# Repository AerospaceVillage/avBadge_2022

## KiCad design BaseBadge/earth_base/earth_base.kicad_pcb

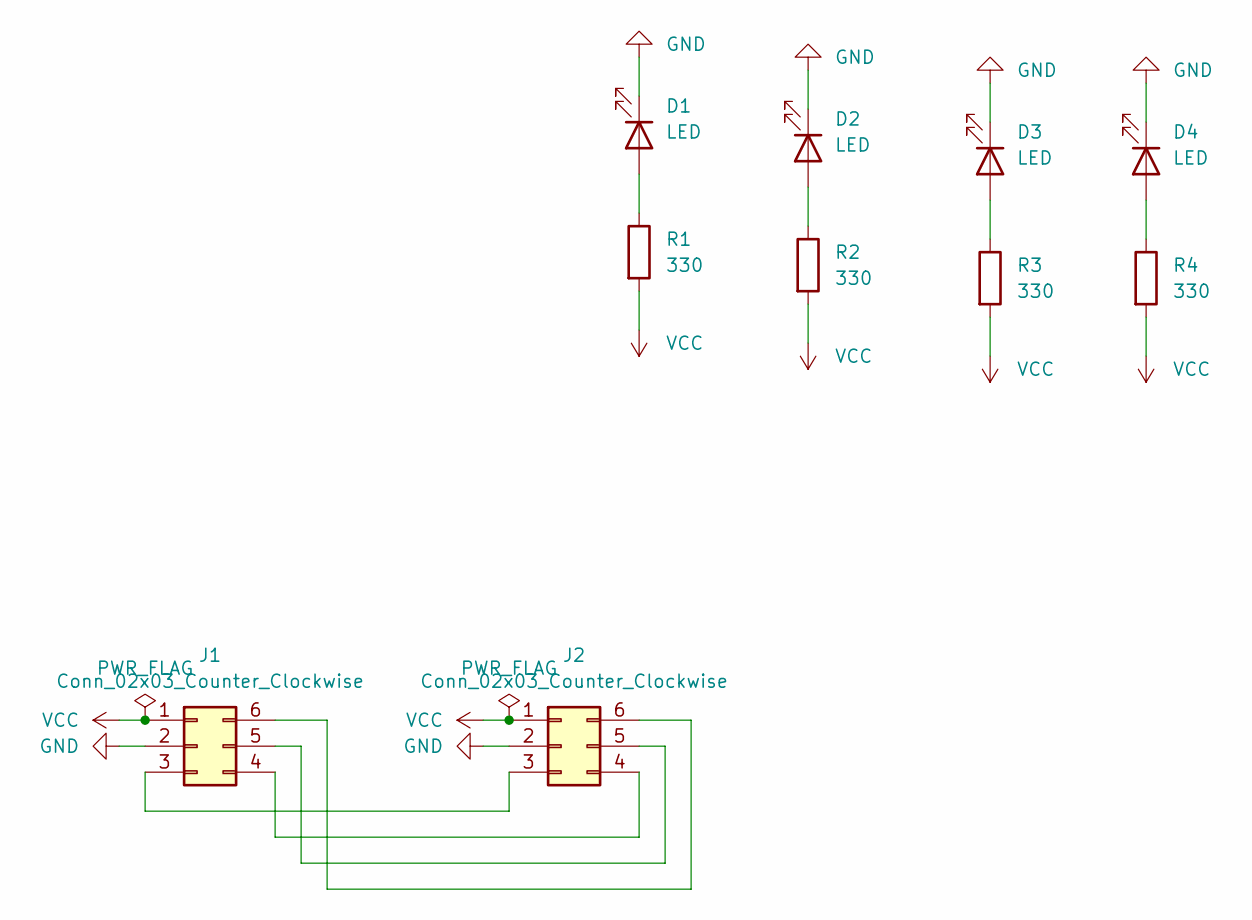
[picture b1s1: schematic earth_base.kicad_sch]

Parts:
D1, D2, D3, D4: LED
J1: Conn_02x03_Counter_Clockwise; sky2ground_connector
J2: Conn_02x03_Counter_Clockwise; PinSocket_2x03_P2.54mm_Vertical
R1, R2, R3, R4: 330; R_0805_2012Metric

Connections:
GND: D1.1 (K), D2.1 (K), D3.1 (K), D4.1 (K), J1.2, J2.2
unnamed: D1.2 (A), R1.1
unnamed: D2.2 (A), R2.1
unnamed: D3.2 (A), R3.1
unnamed: D4.2 (A), R4.1
unnamed: J1.3, J2.3
unnamed: J1.4, J2.4
unnamed: J1.5, J2.5
unnamed: J1.6, J2.6
VCC: J1.1, J2.1, R1.2, R2.2, R3.2, R4.2

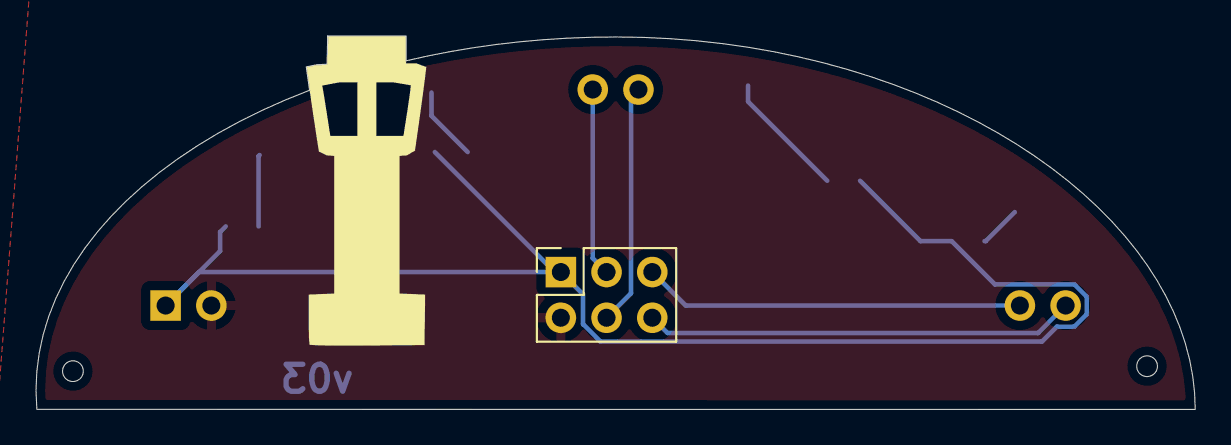
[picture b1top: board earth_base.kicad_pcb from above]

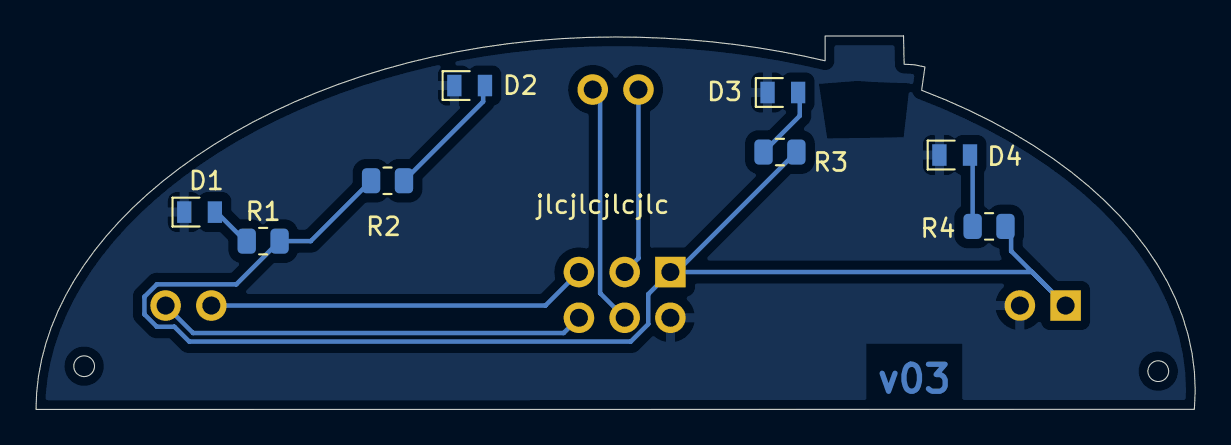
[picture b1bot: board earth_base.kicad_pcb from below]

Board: 2 copper layers, 64.4 x 20.7 mm, 11 parts (8 on the bottom side), 10 nets.

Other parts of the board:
svg2mod: G***; earth_base

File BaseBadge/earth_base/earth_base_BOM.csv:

Comment,Designator,Footprint,LCSC Part Number
330,"R1, R2, R3, R4",Capacitor_SMD:C_0805_2012Metric,C17630
LED,"D1, D2, D3, D4",0603,C72038

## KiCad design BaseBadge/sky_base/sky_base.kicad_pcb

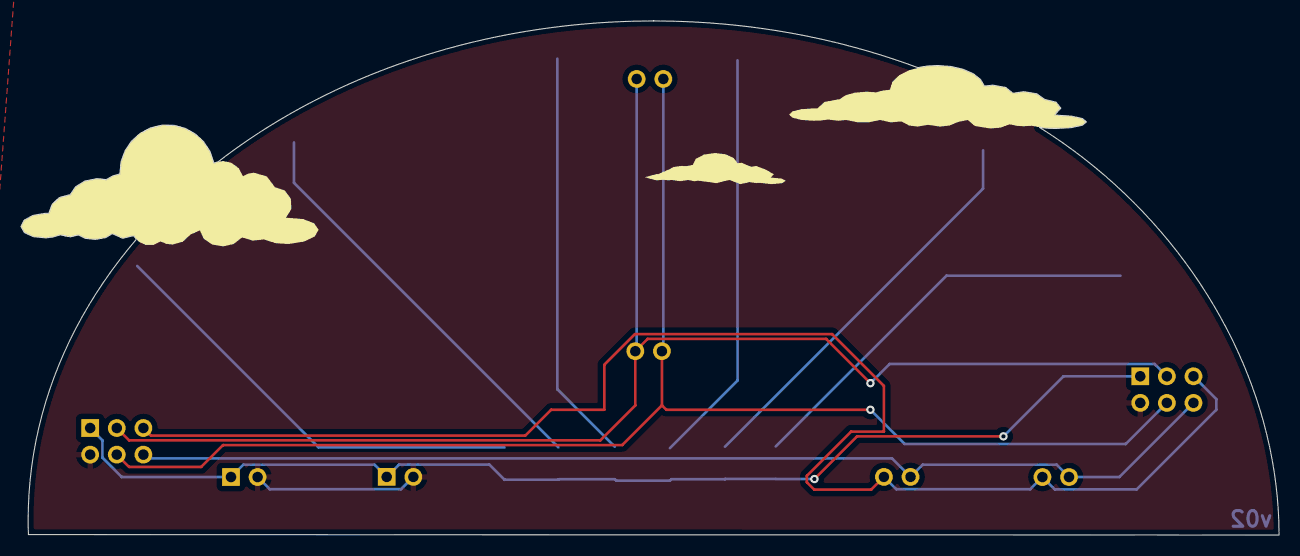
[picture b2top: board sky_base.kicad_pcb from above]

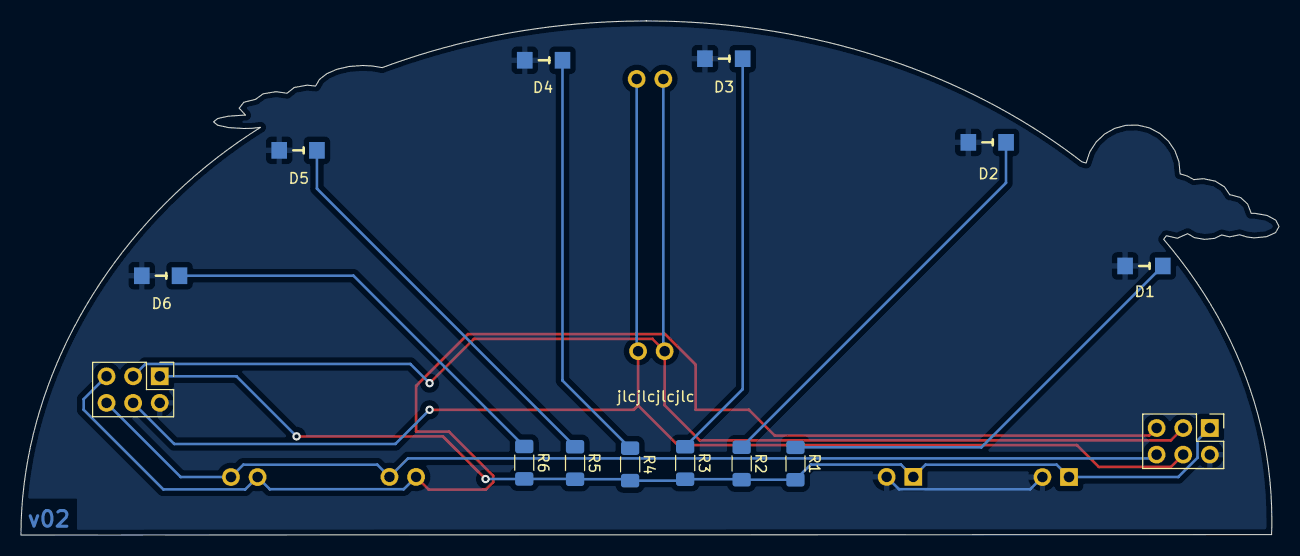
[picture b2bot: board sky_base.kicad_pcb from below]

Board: 2 copper layers, 120.1 x 49.1 mm, 17 parts (14 on the bottom side), 12 nets.

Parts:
D1, D2, D3, D4, D5, D6: LED; APTR3216-VFX
J1, J3: Conn_02x03_Counter_Clockwise; PinHeader_2x03_P2.54mm_Vertical
J2: Conn_02x03_Counter_Clockwise; space2sky_connector
J4: Conn_02x03_Counter_Clockwise; sky2ground_connector
R1, R2, R3, R4, R5, R6: 330; R_1206_3216Metric_Pad1.30x1.75mm_HandSolder
svg2mod: G***; sky_base

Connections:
GND: D1.1 (K), D2.1 (K), D3.1 (K), D4.1 (K), D5.1 (K), D6.1 (K), J1.2, J2.2, J3.2, J4.2
unnamed: D1.2 (A), R1.1
unnamed: D2.2 (A), R2.1
unnamed: D3.2 (A), R3.1
unnamed: D4.2 (A), R4.1
unnamed: D5.2 (A), R5.1
unnamed: D6.2 (A), R6.1
unnamed: J1.4, J2.4, J3.4, J4.4
unnamed: J1.5, J2.5, J3.5, J4.5
unnamed: J1.6, J2.6, J3.6, J4.6
unnamed: J1.3, J2.3, J3.3, J4.3
VCC: J1.1, J2.1, J3.1, J4.1, R1.2, R2.2, R3.2, R4.2, R5.2, R6.2
